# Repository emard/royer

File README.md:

# Royer - simple sinewave oscillator

Schematics and some PCBs practice in kicad
with several variations (BJT, MOSFET, IGBT)
of simple sinewave oscillators, initially 
published by:

    George H. Royer
    Electrical Manufacturing
    December 1954

Royer oscillator uses zero-voltage switching
(ZVS) to the parallel LC resonant circuit. 
Voltage at LC is sinewave when oscillator is unloaded.
More load will more deform the sinewave.

About regulated Royer see:

    Jim Williams
    Linear Technology
    Application note 118
    March 2008

It needs a sufficiently large choke in series
with middle turn of resonant L. If muddle turn is
not available then 2 chokes can be used.

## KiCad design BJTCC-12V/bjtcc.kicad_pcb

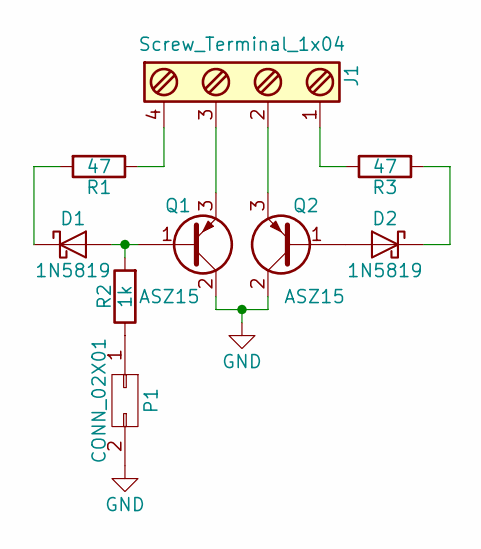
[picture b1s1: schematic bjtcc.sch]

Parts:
D1, D2: 1N5819; Diode_DO-35_SOD27_Horizontal_RM10
J1: Screw_Terminal_1x04; Pin_Header_Straight_1x04
P1: CONN_02X01; SW_PUSH_6mm_h5mm
Q1, Q2: ASZ15; TO-247_PadsOnly_Neutral123
R1, R3: 47; Resistor_Horizontal_RM15mm
R2: 1k; Resistor_Horizontal_RM15mm

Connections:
GND: P1.2, Q1.2 (C), Q2.2 (C)
unnamed: D1.1 (K), R1.2
unnamed: D1.2 (A), Q1.1 (B), R2.2
unnamed: D2.1 (K), R3.2
unnamed: D2.2 (A), Q2.1 (B)
unnamed: J1.1, R3.1
unnamed: J1.2, Q2.3 (E)
unnamed: J1.3, Q1.3 (E)
unnamed: J1.4, R1.1
unnamed: P1.1, R2.1

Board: 2 copper layers, 9 parts (1 on the bottom side), 10 nets, no tracks yet.

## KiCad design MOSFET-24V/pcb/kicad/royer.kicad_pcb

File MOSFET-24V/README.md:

# Low voltage Royer with MOSFET

Using low treshold MOSFETs for supply voltage 9-24V
Schematics starts with supply voltage above 8V.

Supply voltage and recommended max amperage:

     9V 0.5A
    12V 1-0A
    24V 2.0A

Avoid running at low voltage supply voltage <15V and high current
>2A because mosfets gate voltage will not be as steep to quicky
switch therefore they will heat up significantly.

At higher supply voltage, >24V mosfets swich faster and
dissiapte less heat.

The slope of the primary coil of transformer is approx the same
as gate slope. Primary coil amplitude is about 2-3x the supply
voltage. Take into account increased voltage at primary when 
choosing voltage rating for mosfets, capactors and fast diodes.

# PCB

Gerber files can be uploaded to https://www.seeedstudio.com/fusion_pcb.html
they will produce PCB for 10$

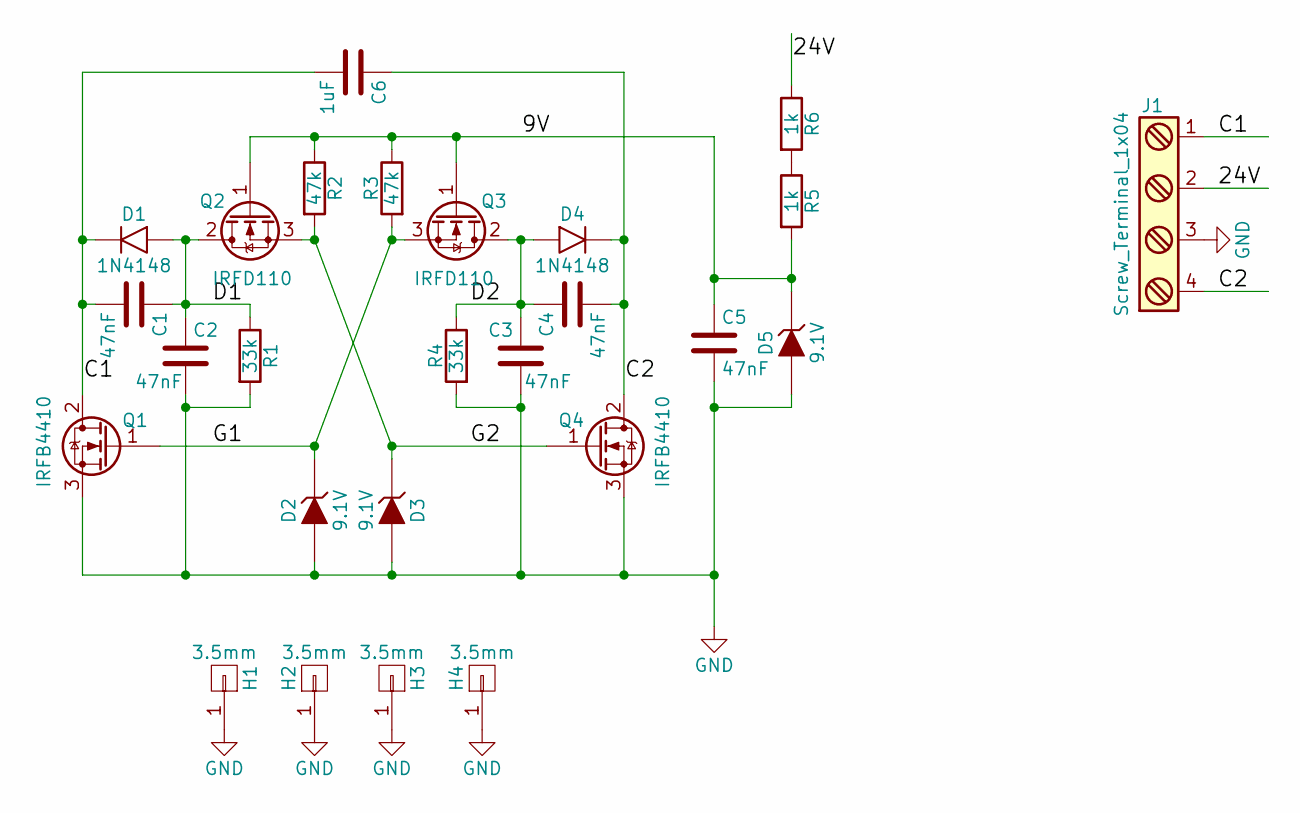
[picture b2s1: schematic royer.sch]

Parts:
C1, C2, C3, C4, C5: 47nF; C_1206_HandSoldering
C6: 1uF; Choke_Horizontal_RM10mm
D1, D4: 1N4148; MiniMELF_Handsoldering
D2, D3, D5: 9.1V; D4
H1, H2, H3, H4: 3.5mm; MountingHole_3.5mm_Pad
J1: Screw_Terminal_1x04; screw-terminal-4-pin
Q1, Q4: IRFB4410; TO-220-small-heatsink
Q2, Q3: IRFD110; DIP-4_W7.62mm_LongPads
R1, R4: 33k; R_1206_HandSoldering
R2, R3: 47k; R_1206_HandSoldering
R5, R6: 1k; R_1206_HandSoldering

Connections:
/9V: C5.1, D5.1 (K), Q2.1 (G), Q3.1 (G), R2.1, R3.1, R5.2
/24V: J1.2, R6.1
/C1: C1.2, C6.2, D1.1 (K), J1.1, Q1.2 (D)
/C2: C4.2, C6.1, D4.1 (K), J1.4, Q4.2 (D)
/D1: C1.1, C2.1, D1.2 (A), Q2.2 (D), R1.1
/D2: C3.1, C4.1, D4.2 (A), Q3.2 (D), R4.1
/G1: D2.1 (K), Q1.1 (G), Q3.3 (S), R3.2
/G2: D3.1 (K), Q2.3 (S), Q4.1 (G), R2.2
GND: C2.2, C3.2, C5.2, D2.2 (A), D3.2 (A), D5.2 (A), H1.1, H2.1, H3.1, H4.1, J1.3, Q1.3 (S), Q4.3 (S), R1.2, R4.2
unnamed: R5.1, R6.2

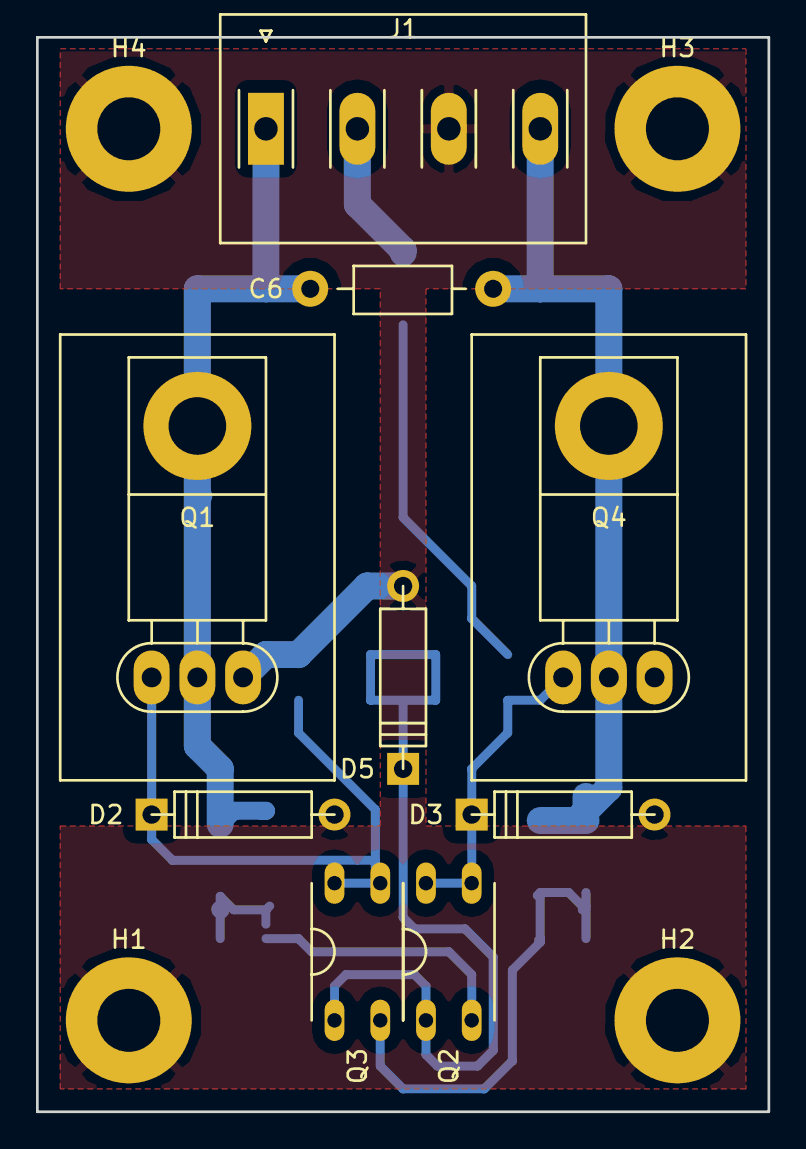
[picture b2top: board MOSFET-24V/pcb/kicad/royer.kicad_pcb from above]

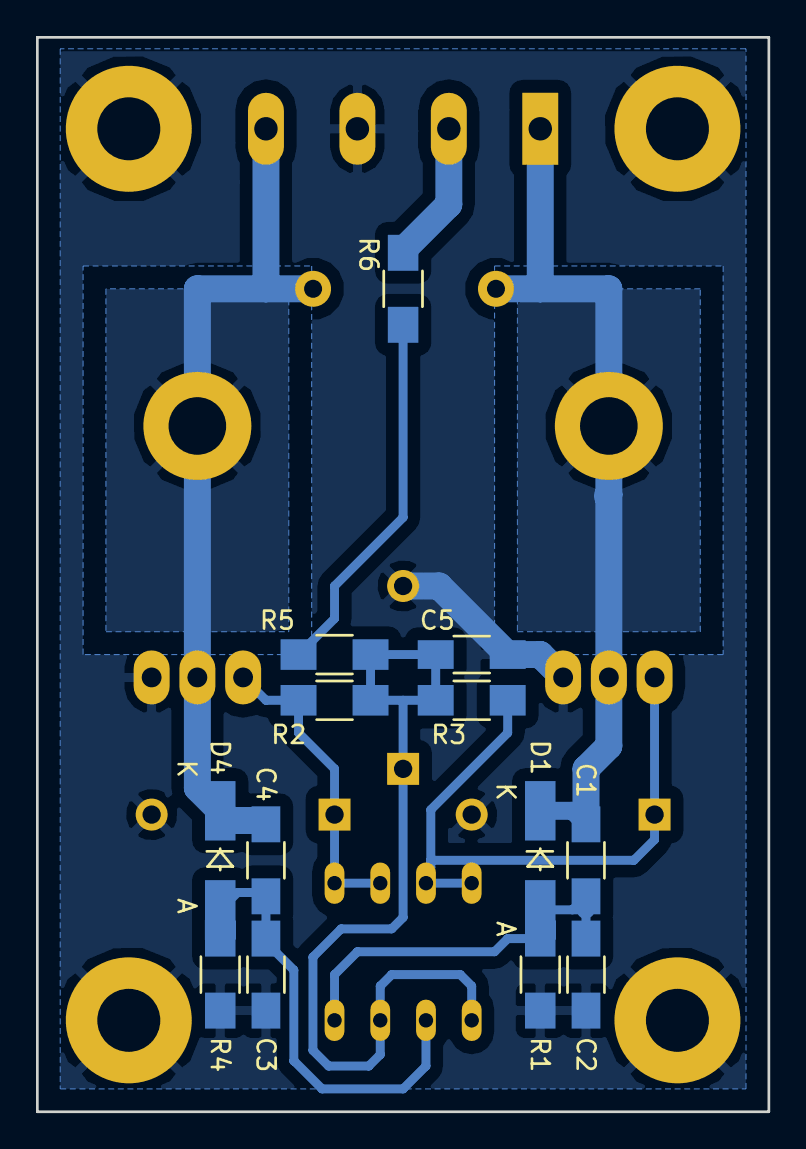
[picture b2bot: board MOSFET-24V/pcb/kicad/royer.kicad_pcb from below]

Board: 2 copper layers, 40.6 x 59.7 mm, 26 parts (13 on the bottom side), 10 nets.

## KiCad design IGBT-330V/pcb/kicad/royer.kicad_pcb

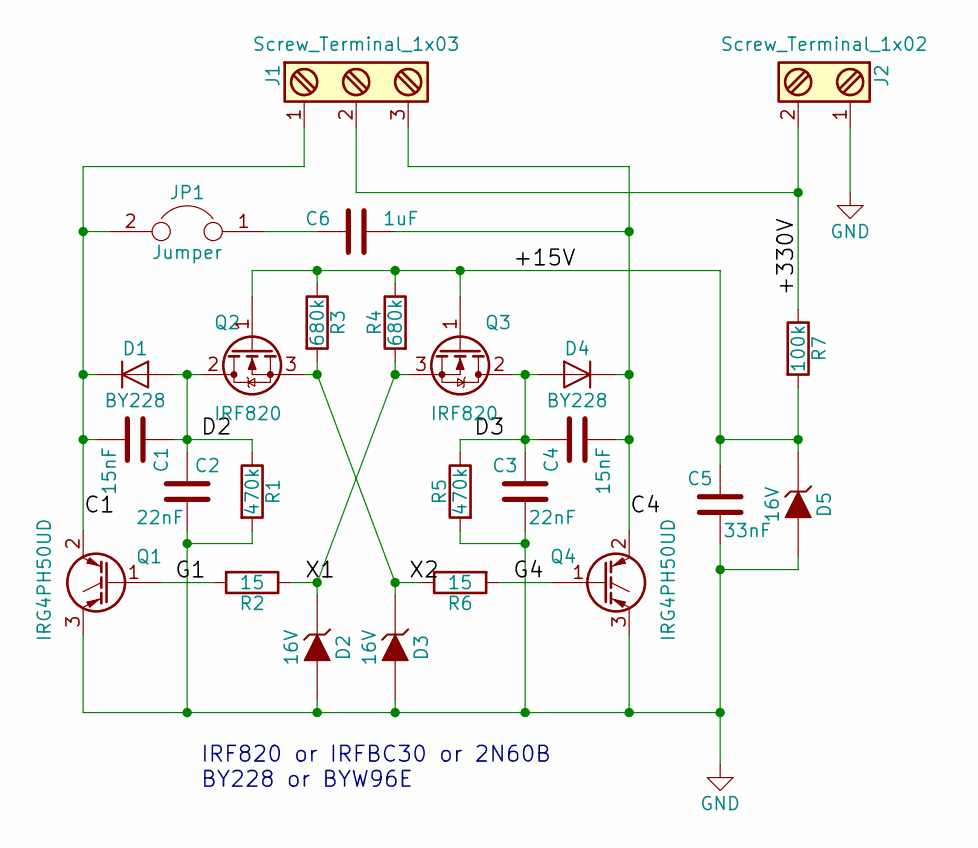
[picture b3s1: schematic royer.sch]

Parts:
C1, C4: 15nF; C_Rect_L27_W9_H17_P23
C2, C3: 22nF; C_Rect_L27_W9_H17_P23
C5: 33nF; C_Rect_L27_W9_H17_P23
C6: 1uF; C_Rect_L27_W9_H17_P23
D1, D4: BY228; Diode_DO-201AD_Horizontal_RM15
D2, D3, D5: 16V; D6
J1: Screw_Terminal_1x03; TerminalBlock_WAGO-804_RM5mm_3pol
J2: Screw_Terminal_1x02; TerminalBlock_WAGO-804_RM5mm_2pol
JP1: Jumper; TerminalBlock_Pheonix_MPT-2.54mm_2pol
Q1, Q4: IRG4PH50UD; TO-247_Vertical_Neutral123_largePads
Q2, Q3: IRF820; TO-220_Neutral123_Vertical_LargePads
R1, R5: 470k; Resistor_Horizontal_RM15mm
R2, R6: 15; Resistor_Horizontal_RM20mm
R3, R4: 680k; Resistor_Horizontal_RM15mm
R7: 100k; Resistor_Horizontal_RM15mm

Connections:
/+15V: C5.1, D5.1 (K), Q2.1 (G), Q3.1 (G), R3.1, R4.1, R7.2
/+330V: J1.2, J2.2, R7.1
/C1: C1.2, D1.1 (K), J1.1, JP1.2, Q1.2 (C)
/C4: C4.2, C6.1, D4.1 (K), J1.3, Q4.2 (C)
/D2: C1.1, C2.1, D1.2 (A), Q2.2 (D), R1.1
/D3: C3.1, C4.1, D4.2 (A), Q3.2 (D), R5.1
/G1: Q1.1 (G), R2.2
/G4: Q4.1 (G), R6.2
/X1: D2.1 (K), Q3.3 (S), R2.1, R4.2
/X2: D3.1 (K), Q2.3 (S), R3.2, R6.1
GND: C2.2, C3.2, C5.2, D2.2 (A), D3.2 (A), D5.2 (A), J2.1, Q1.3 (E), Q4.3 (E), R1.2, R5.2
unnamed: C6.2, JP1.1

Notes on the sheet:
IRF820 or IRFBC30 or 2N60B BY228 or BYW96E

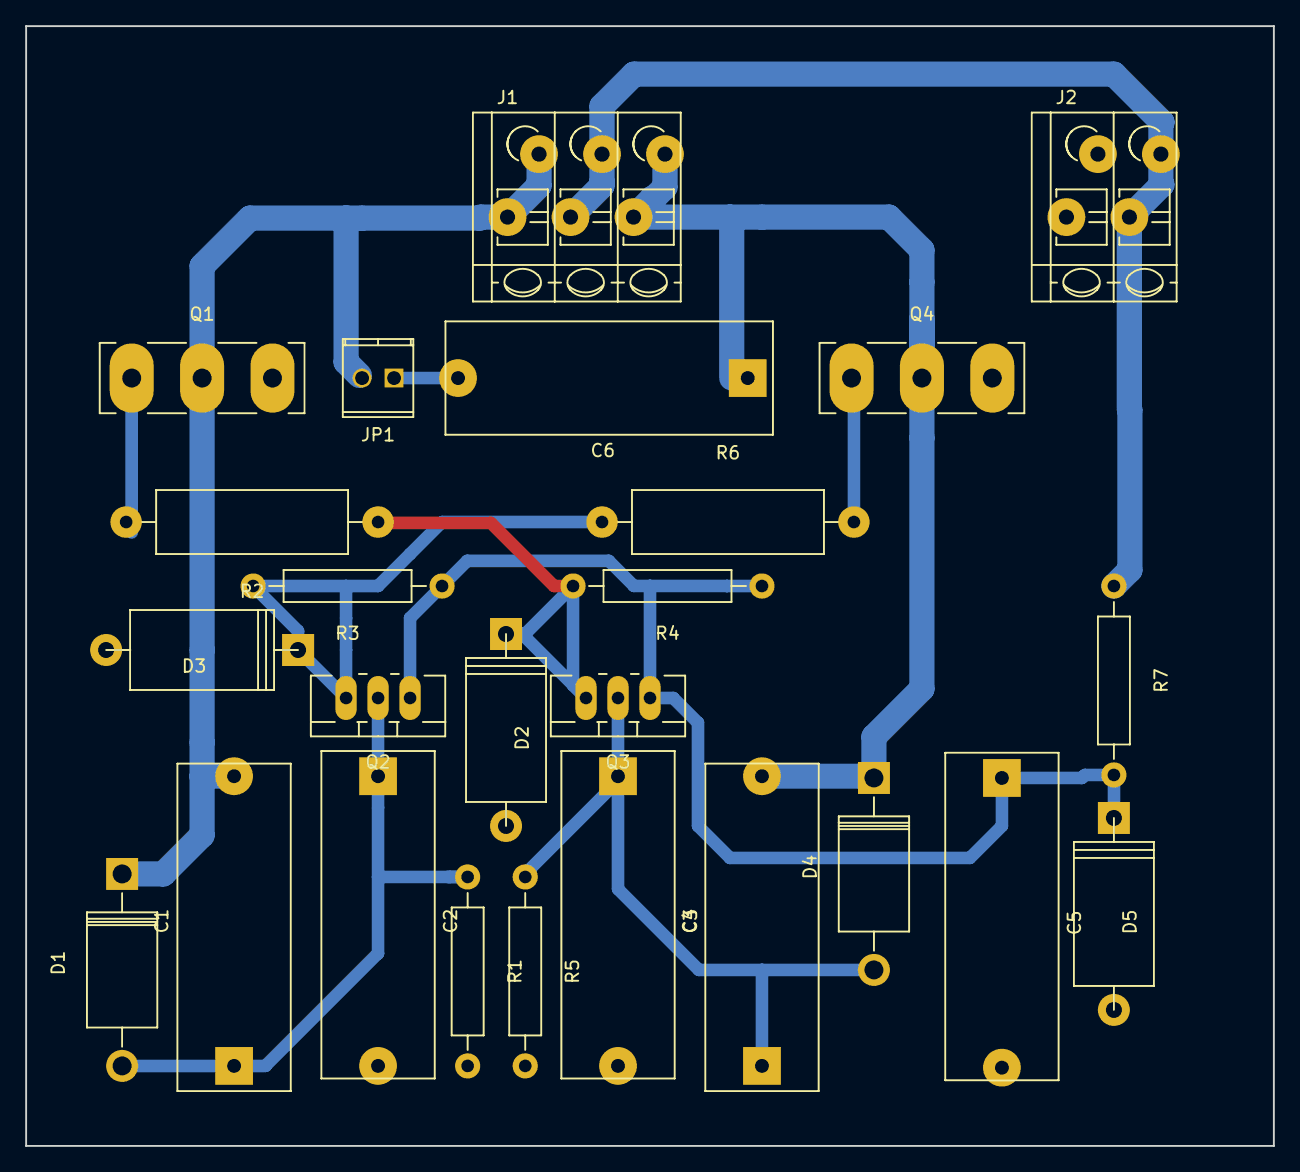
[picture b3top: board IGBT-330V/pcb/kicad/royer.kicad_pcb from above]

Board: 2 copper layers, 99.1 x 88.9 mm, 25 parts (0 on the bottom side), 12 nets.

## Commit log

2017-04-16 simple schematics of basic royer oscillator with BJT transistors
2017-04-16 Low voltage MOSFET 9-24V
2017-04-16 picture of protoboard and readme
2017-04-16 high voltage IGBT 30-330V
2017-04-16 some comments and pictures
2017-04-16 move kicad to PCB subdirectory
2017-04-16 net labels
2017-04-16 rearranging SMD components
2017-04-16 fixing GND on the schematics
2017-04-16 better component placement, single-sided PCB
2017-04-16 symmetry on the PCB
2017-04-16 gerber update
2017-04-16 rearranging components, routed
2017-04-17 optimizing component placement
2017-04-17 correct footprint for DIL-4 power mosfet
2017-04-17 stack DIL-4 end-to-end to fit into a single DIL-8 socket
2017-04-17 compacting PCB
2017-04-17 enlarging holes 3.2->3.5 mm# Please enter the commit message for your changes. Lines starting
2017-04-17 Readme update
2017-04-22 footprint for small TO-220 heatsink
2017-04-22 compacting PCB (using only 4 screw terminals)
2017-04-22 updating gerbers
2017-04-22 git add TO-220 footprint with small heatsing (late commit)
2017-04-22 updating jpg
2017-04-22 increasing drill hole sizes in to-220 and screw terminal footprints
2017-04-22 plot to seeedstudio rules
2017-04-23 small changes to reflect production
2017-04-23 board send to production
2017-04-23 last minute change (too late for production) TO-220 pads placed only on bottom layer to avoid short-circuit with mounted heatsink
2017-04-26 PCB production
2017-04-27 pcb fill layer not rebuild after hole repositioned. It is now corrected and top GND layer is added. Sent to production
2017-05-09 initial commit of BJT common-collector schematics
2017-05-09 rough placing footprints on PCB
2017-05-09 .gitignore file
2017-05-09 moving to "pcb" directory
2017-05-09 updating .pro files
2017-05-09 schematics PDF
2017-05-09 moving to "kicad/pcb" directory
2017-05-14 BJT version with Si and Ge
2017-05-15 changing values on MOSFET circuit
2017-05-16 Change from 10nF/10nF to 22nF/10nF capacitive divider
2017-05-16 revert back to 10nF
2017-05-16 gerbers update
2017-05-18 Cn 22nF comment
